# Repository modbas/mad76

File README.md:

author: Frank Tränkle[^1]  
Hochschule Heilbronn, Germany
bibliography: ../lib/bib.bib
csl: ../lib/ieee.csl
link-citations: true
reference-section-title: References
title: Mini-Auto-Drive MAD76

MAD76 Features
==============

-   Autonomous Driving in 1:76 scale

-   Multi-player robot car racing

-   Race against AI cars using Xbox controllers

-   Program your own AI

-   100 x 50cm tracks

-   Fits in a backpack for easy transport

-   @home @school @university @automotive partners @open source
    @Hochschule Heilbronn @Automotive Systems Engineering

-   \#Computer Vision \#Motion Planning \#Motion Control \#Deep Neural
    Networks \#Reinforcement Learning \#Raspberry Pi Programmming \#C++
    Coding \#Python Coding \#MATLAB/Simulink Simulation \#ROS2

-   <https://www.youtube.com/@ft7894>

MAD76 Kit
=========

-   Turboracing 1:76 RC cars (<https://www.turboracing.net>)

-   Raspberry Pi Global Shutter Camera is mounted in topview on tripod

-   Raspberry Pi 5 runs Raspberry Pi OS (Debian Linux)

-   MAD76 Driving Stack is implemented as software components in
    middleware ROS2 (<https://docs.ros.org/en/jazzy/index.html>)

-   MAD76 Driving Stack consists of the following software components:

    -   Computer Vision reads in frames from topview camera and detects
        cars by ArUco markers

    -   Multi-Object Tracking computes the cars’ velocities

    -   Motion Planning computes optimal trajectories

    -   Motion Control controls the cars on the trajectories

-   MAD76 Driving Stack is programmed in C++, Python

-   MAD76 Driving Stack may run in a distributed computer environment
    (Raspberry Pi and Linux-PCs)

-   Optional Linux-PCs are for race simulation, programming,
    MATLAB/Simulink simulation, AI agents training

-   MAD76 is open source

-   Contributions are greatly welcome

-   [Installation Guide](doc/install/install.md)
    ([install.pdf](doc/install/install.pdf))

MAD76 Academy
=============

MAD76 Academy offers a variety of learning lessons to get started with
your MAD76 kit. To configure and start MAD76 car racing without any
programming efforts, please follow modules B and C.

-   [A. Linux Basics](doc/teachlinux/teachlinux.md)
    ([teachlinux.pdf](doc/teachlinux/teachlinux.pdf))

-   [B. Adjust MAD76](doc/teachadjust/teachadjust.md)
    ([teachadjust.pdf](doc/teachadjust/teachadjust.pdf))

-   [C. Start Car Race](doc/teachrace/teachrace.md)
    ([teachrace.pdf](doc/teachrace/teachrace.pdf))

-   [D. Python Basics](doc/teachpython/teachpython.md)
    ([teachpython.pdf](doc/teachpython/teachpython.pdf))

-   [E. MAD76 I/O Programming](doc/teachmad76io/teachmad76io.md)
    ([teachmad76io.pdf](doc/teachmad76io/teachmad76io.pdf))

-   [F. ROS2 Coding for MAD76](doc/teachros/teachros.md)
    ([teachros.pdf](doc/teachros/teachros.pdf))

-   [G. MAD76 SQL Database](doc/teachsql/teachsql.md)
    ([teachsql.pdf](doc/teachsql/teachsql.pdf))

-   [H. Model-Based Software Engineering with
    MATLAB/Simulink](doc/teachmatlab/teachmatlab.md)
    ([teachmatlab.pdf](doc/teachmatlab/teachmatlab.pdf))

You may further start a Bachelor- or Master-degree study program at
[Hochschule
Heilbronn](https://www.hs-heilbronn.de/en/automotive-systems-engineering)
to deepen your knowledge in

-   autonomous car racing with MAD76

-   autonomous systems, in general

-   automotive systems engineering

-   robotics

-   control theory

-   artificial intelligence

-   embedded software engineering

and get ready for a career in the automotive or robotics industry.

[^1]: frank.traenkle@hs-heilbronn.de

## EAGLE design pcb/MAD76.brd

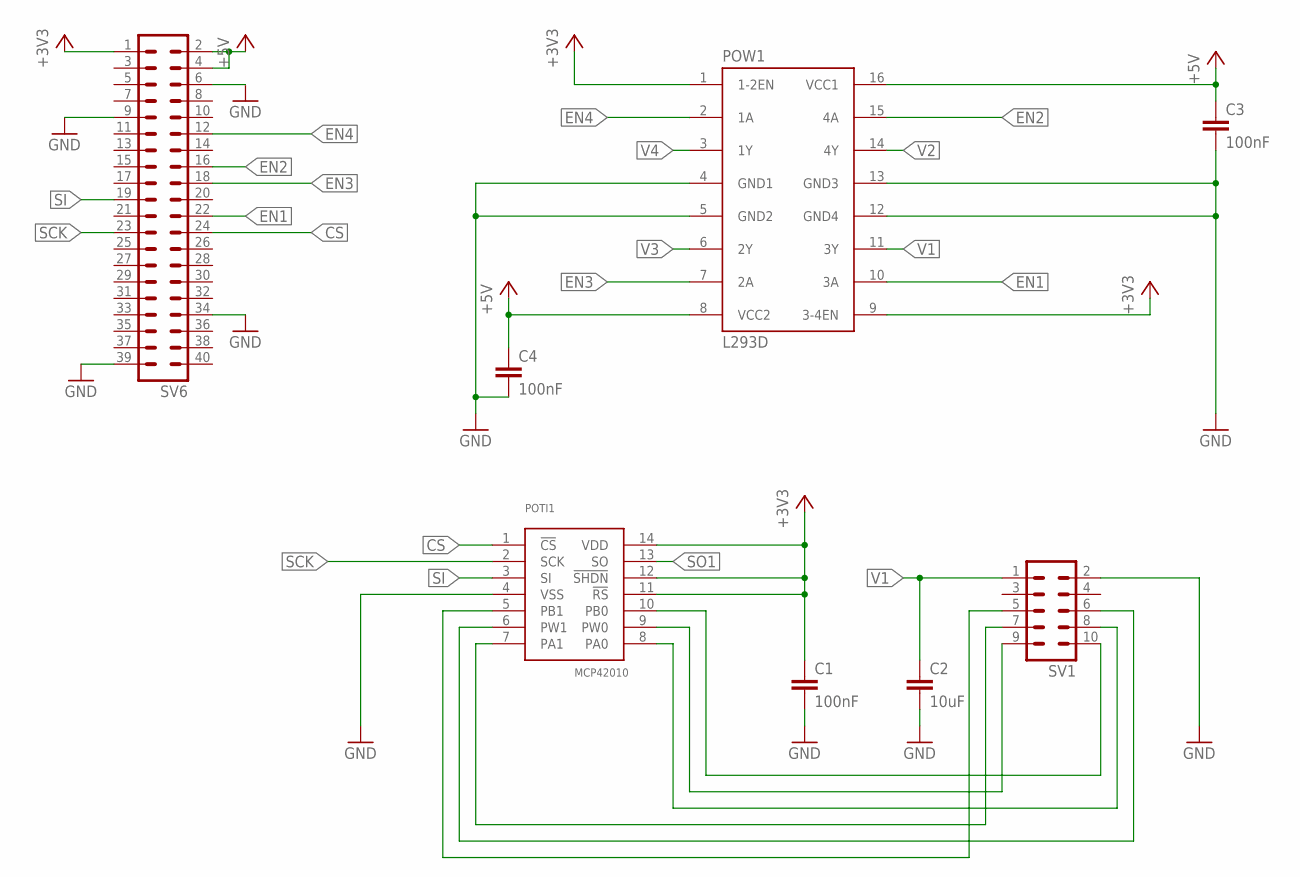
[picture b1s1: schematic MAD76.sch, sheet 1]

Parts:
C1, C3, C4: 100nF; C0805
C2: 10uF; C0805
POTI1: MCP42010; DIL14
POW1: L293D; DIL16
SV1: ML10
SV6: MA20-2W_RPI

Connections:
+3V3: C1.1, POTI1.11 (!RS), POTI1.12 (!SHDN), POTI1.14 (VDD), POW1.1 (1-2EN), POW1.9 (3-4EN), SV6.1; also elsewhere on the board
+5V: C3.1, C4.1, POW1.8 (VCC2), POW1.16 (VCC1), SV6.2, SV6.4
CS: POTI1.1 (!CS), SV6.24; also elsewhere on the board
EN1: POW1.10 (3A), SV6.22
EN2: POW1.15 (4A), SV6.16
EN3: POW1.7 (2A), SV6.18
EN4: POW1.2 (1A), SV6.12
GND: C1.2, C2.2, C3.2, C4.2, POTI1.4 (VSS), POW1.4 (GND1), POW1.5 (GND2), POW1.12 (GND4), POW1.13 (GND3), SV1.2, SV6.6, SV6.9, SV6.34, SV6.39; also elsewhere on the board
PA1.0: POTI1.8 (PA0), SV1.8
PA1.1: POTI1.7 (PA1), SV1.7
PB1.0: POTI1.10 (PB0), SV1.10
PB1.1: POTI1.5 (PB1), SV1.5
PW1.0: POTI1.9 (PW0), SV1.9
PW1.1: POTI1.6 (PW1), SV1.6
SCK: POTI1.2 (SCK), SV6.23; also elsewhere on the board
SI: POTI1.3 (SI), SV6.19
SO1: POTI1.13 (SO); also elsewhere on the board
V1: C2.1, POW1.11 (3Y), SV1.1
V2: POW1.14 (4Y); also elsewhere on the board
V3: POW1.6 (2Y); also elsewhere on the board
V4: POW1.3 (1Y); also elsewhere on the board

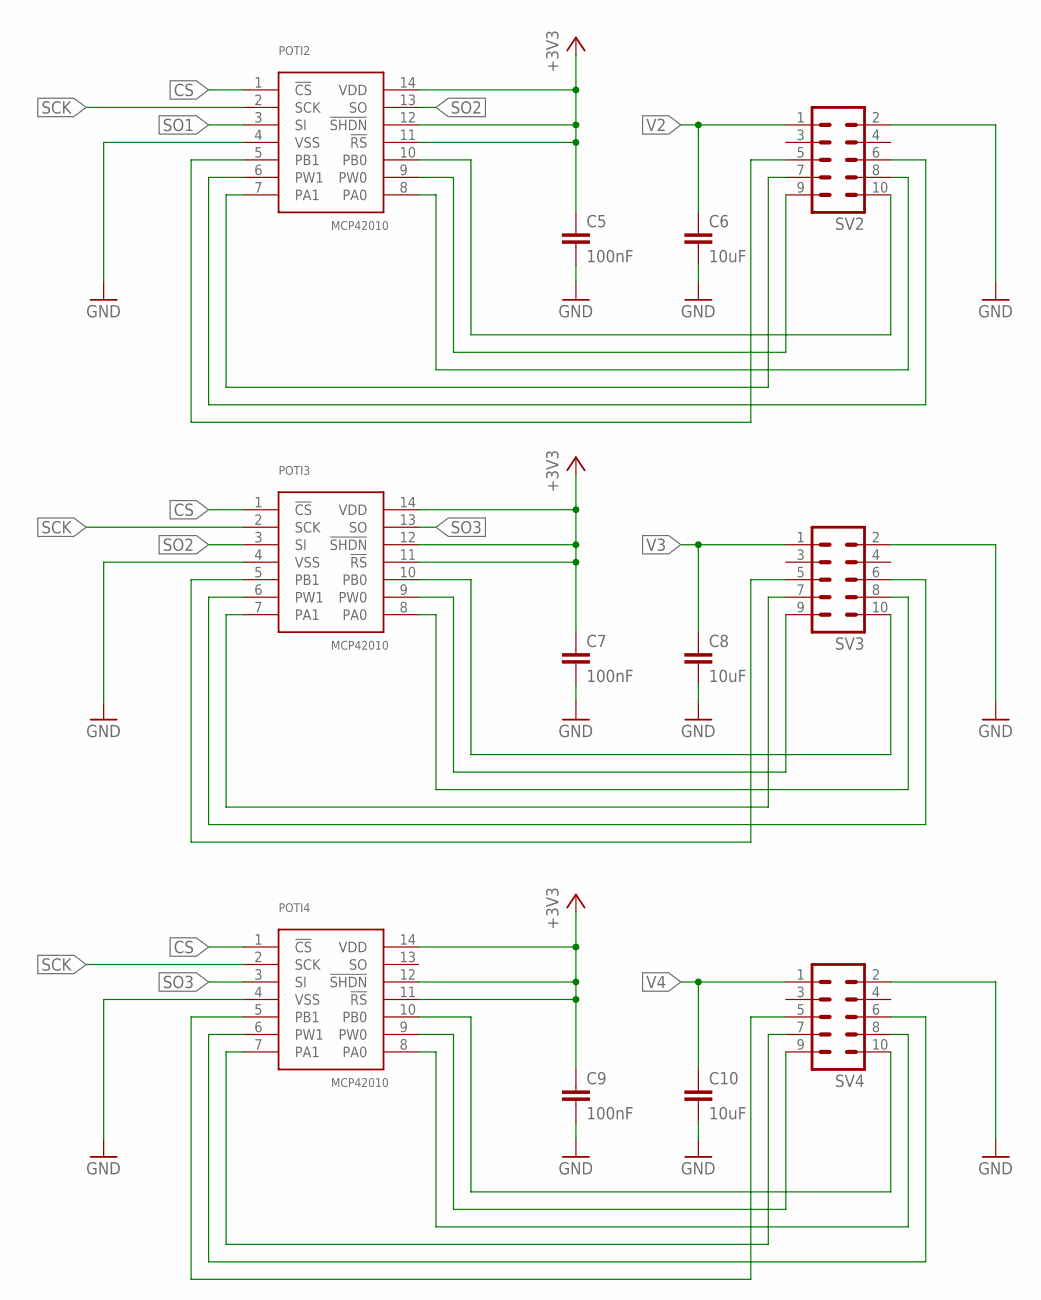
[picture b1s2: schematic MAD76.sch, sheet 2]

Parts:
C5, C7, C9: 100nF; C0805
C6, C8, C10: 10uF; C0805
POTI2, POTI3, POTI4: MCP42010; DIL14
SV2, SV3, SV4: ML10

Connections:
+3V3: C5.1, C7.1, C9.1, POTI2.11 (!RS), POTI2.12 (!SHDN), POTI2.14 (VDD), POTI3.11 (!RS), POTI3.12 (!SHDN), POTI3.14 (VDD), POTI4.11 (!RS), POTI4.12 (!SHDN), POTI4.14 (VDD); also elsewhere on the board
CS: POTI2.1 (!CS), POTI3.1 (!CS), POTI4.1 (!CS); also elsewhere on the board
GND: C5.2, C6.2, C7.2, C8.2, C9.2, C10.2, POTI2.4 (VSS), POTI3.4 (VSS), POTI4.4 (VSS), SV2.2, SV3.2, SV4.2; also elsewhere on the board
PA2.0: POTI2.8 (PA0), SV2.8
PA2.1: POTI2.7 (PA1), SV2.7
PA3.0: POTI3.8 (PA0), SV3.8
PA3.1: POTI3.7 (PA1), SV3.7
PA4.0: POTI4.8 (PA0), SV4.8
PA4.1: POTI4.7 (PA1), SV4.7
PB2.0: POTI2.10 (PB0), SV2.10
PB2.1: POTI2.5 (PB1), SV2.5
PB3.0: POTI3.10 (PB0), SV3.10
PB3.1: POTI3.5 (PB1), SV3.5
PB4.0: POTI4.10 (PB0), SV4.10
PB4.1: POTI4.5 (PB1), SV4.5
PW2.0: POTI2.9 (PW0), SV2.9
PW2.1: POTI2.6 (PW1), SV2.6
PW3.0: POTI3.9 (PW0), SV3.9
PW3.1: POTI3.6 (PW1), SV3.6
PW4.0: POTI4.9 (PW0), SV4.9
PW4.1: POTI4.6 (PW1), SV4.6
SCK: POTI2.2 (SCK), POTI3.2 (SCK), POTI4.2 (SCK); also elsewhere on the board
SO1: POTI2.3 (SI); also elsewhere on the board
SO2: POTI2.13 (SO), POTI3.3 (SI)
SO3: POTI3.13 (SO), POTI4.3 (SI)
V2: C6.1, SV2.1; also elsewhere on the board
V3: C8.1, SV3.1; also elsewhere on the board
V4: C10.1, SV4.1; also elsewhere on the board

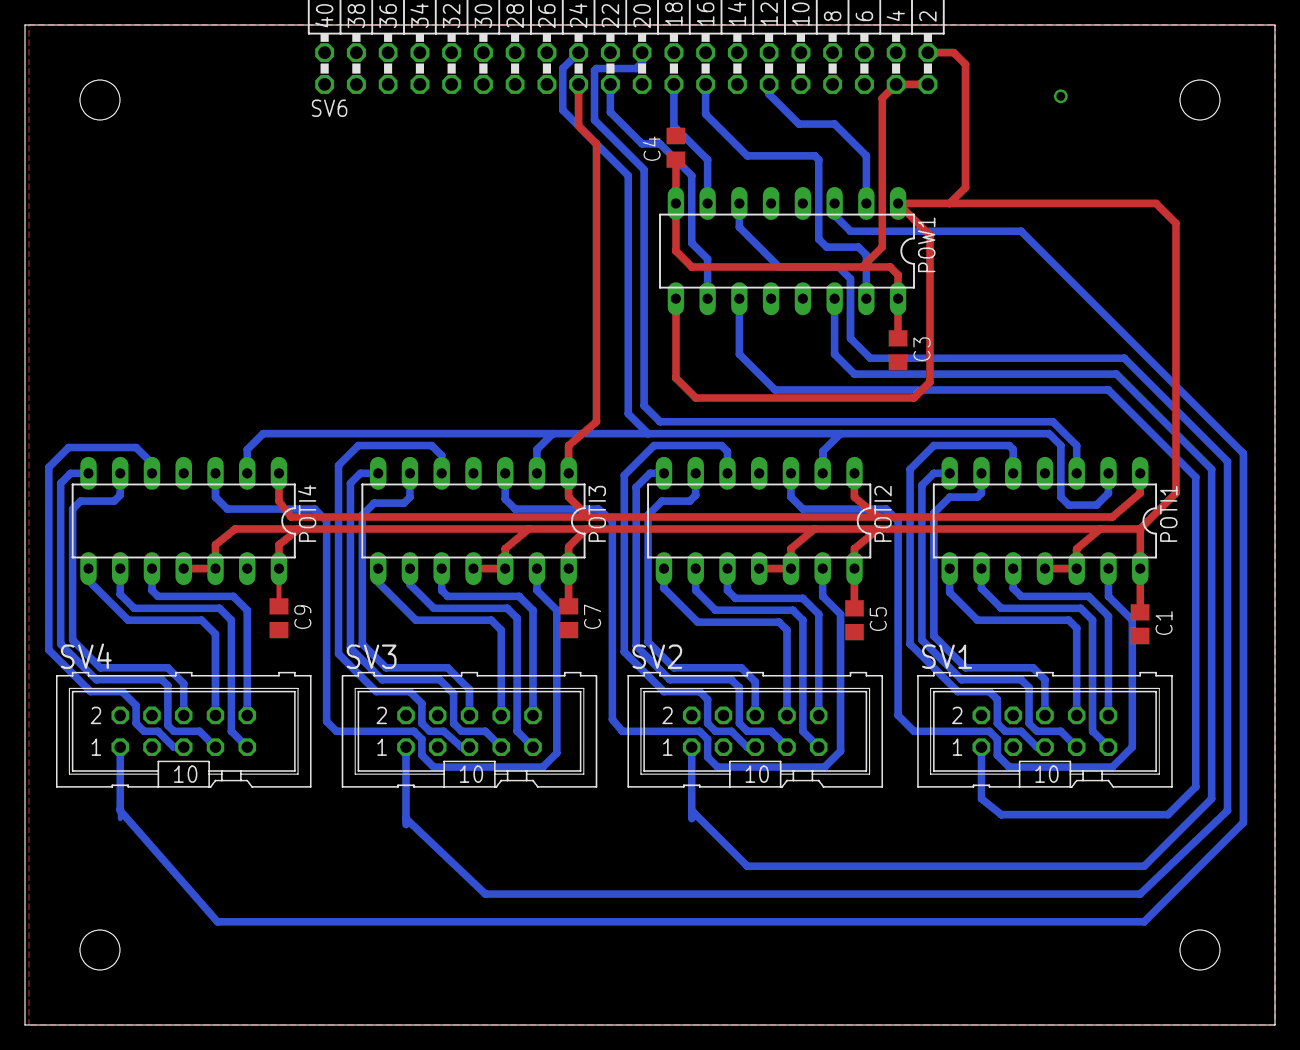
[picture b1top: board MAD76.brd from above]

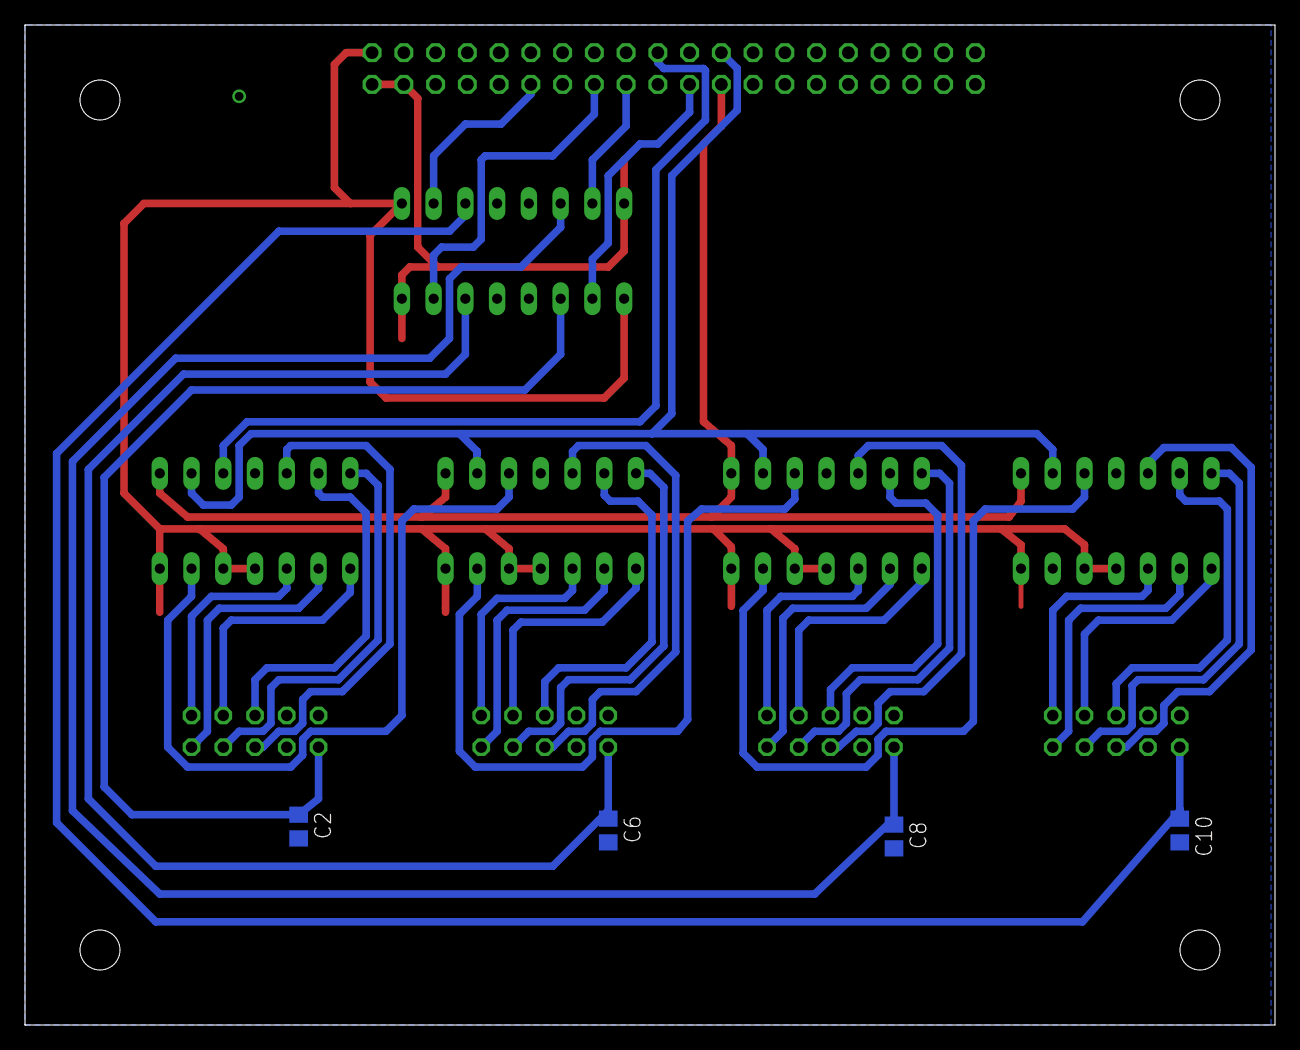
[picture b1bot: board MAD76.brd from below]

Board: 2 copper layers, 100.0 x 80.0 mm, 20 parts (4 on the bottom side), 41 nets.

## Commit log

2024-11-10 reformatting
2024-11-10 README generated from LaTeX
2024-11-10 vision doc
2024-11-10 foto added
2024-11-10 README.md is now in root folder
2024-11-10 link fixed
2024-11-29 inkscape latex
2024-11-30 test
2024-11-30 test removed
2024-11-30 test deleted
2024-12-01 install markdown
2024-12-21 MAD76 Box
2024-12-21 link to installation guide
2024-12-21 now with bib
2024-12-21 markdown gfm format
2024-12-22 MAD76 ROS2 workspace
2024-12-22 conditional install of scripts and launch dirs
2024-12-22 bib references updated
2024-12-23 install ROS2, MAD76
2024-12-23 missing figure captions added
2024-12-23 big foto removed
2024-12-25 MAD76 SiL architecture
2024-12-28 missing source for ros_ws
2024-12-28 support of other distributions for SiL
2024-12-28 reference to section fixed
2025-02-05 BOM updated, marker generation
2025-02-05 CurbCtrlNode deactivated
2025-02-25 ROS2 Jazzy
2025-08-03 set exposure workaround, race management
2025-08-03 install flask, peewee
2025-08-10 MAD76 Academy for Linux, Python
2025-08-10 aligned fixed
2025-08-10 github pages
2025-08-10 use table instead of eqnarray
2025-08-10 use 55253
2025-08-12 MATLAB templates and lib
2025-08-12 c71_car0_template running
2025-08-12 MATLAB installation
2025-08-12 typos fixed
2025-08-17 remote control, MAD I/O prog
2025-08-17 links to teachmad76io
2025-08-17 relative href
2025-08-24 learning sessions MAD76 IO, ROS2
2025-08-24 learning lesson ROS2
2025-08-24 eq labels, figure fixed
2025-08-24 link to ROS2 lesson fixed
2025-08-24 href fixed
2025-08-24 lstlisting fixed
2025-08-24 missing madpicamrc.launch added
2025-08-24 mbmadrclib.py fixed
2025-08-25 environments exercises and multicols fixed
2025-08-25 PDFs added
2025-08-25 PDFs in slides format
2025-08-29 review of lessons
2025-09-15 foto of lab system
2025-09-16 L293B examples
2025-09-16 ctrlnode.py added
2025-09-16 setup.py added
2025-09-17 reviewed teaching modules
2025-09-17 ideal line
2025-09-19 send_maneuver.py starts all cars
2025-09-20 race manual
2025-09-20 handout and slides
2025-09-20 math formatting fixed
2025-09-20 references fixed
2025-09-21 typo fixed
2025-09-28 teachsql added
2025-10-05 s06_sig_template.slx with carobs
2025-10-07 without lib refs
2025-10-08 SQL database string fixed
2025-10-10 new exercise Xbox steering
2025-10-15 Create track_preview.jpg
    preview of track
2025-10-15 created launch files for the nodes
2025-10-15 Create track_preview_out.jpg
    rendering of the overlay_preview.py file
2025-10-15 added camera overlay script
2025-10-15 updated track preview
2025-10-15 Add mgmt_url as ROS parameter in OverlayNode
2025-10-15 remove for development
2025-10-17 Add track preview camera overlay image
    Added a new image file 'track_preview_out_camera_overlay.jpg' to the overlay directory for use as a camera overlay in the project.
2025-10-17 Add test script for overlay preview rendering
    Introduces test_overlay_local.py to generate a preview image with leaderboard and status overlays for local testing. The script loads or creates a placeholder image, applies overlays, and saves the r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
2025-10-17 missing commands fixed
2025-10-31 figure fixed
2025-11-28 emergency stop in mbmadrcpi
2025-12-01 c71_car0_template now loads s06_data.m
2025-12-01 MATLAB simulation on MAD76
2026-01-19 template for SAC agent
2026-02-21 formats fixed
2026-02-21 new c71*.slx with carobs
2026-02-25 new chapters
2026-02-25 links fixed
2026-02-25 module MATLAB/Simulink
2026-02-25 SAC agents in car race
2026-02-25 car race with rqtplot
2026-03-04 EKF model added
2026-03-15 tilde display fixed
2026-03-16 mask removed
2026-03-18 rate transition NoOp
2026-03-20 new c48 agent
2026-03-24 mbc_car_display fixed
2026-04-29 new SAC agents
